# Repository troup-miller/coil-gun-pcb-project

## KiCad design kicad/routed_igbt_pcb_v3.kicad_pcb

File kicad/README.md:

# IGBT PCB — KiCad Project Hand-off

This folder contains a KiCad 7+ project generated from the validated schematic
(`../igbt_schematic.svg` and `../igbt_schematic_notes.md`).

The goal: give you a clean starting point that you open in KiCad, refine,
and route into fab-ready Gerbers, rather than wrestling with the hand-rolled
Gerbers in `../gerber/` which had three known shorts.

## Files

| File | Purpose |
|------|---------|
| `igbt_pcb.kicad_pro` | KiCad project file. Open this in KiCad first. |
| `igbt_pcb.kicad_pcb` | PCB layout with all 26 components placed at their intended positions, ratsnest visible, **no traces yet**. Open in pcbnew. |
| `igbt_pcb.net` | KiCad EESchema-format netlist. 11 nets, 46 pin connections. Defines what connects to what. |
| `igbt_pcb_bom.csv` | Bill of materials with refdes, value, footprint, description. |

## How to use

### Path A: Open the PCB and route directly (fastest)

1. Open KiCad → File → Open Project → select `igbt_pcb.kicad_pro`
2. Open the PCB editor (pcbnew): click `igbt_pcb.kicad_pcb`
3. Components are pre-placed at the coordinates from the schematic intent.
4. **Update footprints from library:** Tools → Update Footprints from Library.
   The footprint *names* in this file are real KiCad library names; pcbnew
   will pull in proper pad geometry, courtyards, silk, etc. on this step.
5. Look at the ratsnest (thin blue lines between pads). Route them as traces
   using your preferred method:
   - Manual: select start pad, "X" to draw track, follow ratsnest
   - Autorouter: Tools → External Plugin → FreeRouting (if installed)
   - Or export to FreeRouting (.dsn export), route, re-import the .ses session
6. Layout intent priorities (from `../igbt_schematic_notes.md` §6):
   - Bottom layer (B.Cu): fill with a continuous **POWER_GROUND** zone (Add Filled Zone → Net = POWER_GROUND → layer = B.Cu)
   - Snubber loop (C1↔R4↔Q1.P3/P4) area < 2 cm²
   - Kelvin lane (Q1.P2 → R3.P2 → D2.P2 → C2.P2 → C3.P2 → U1.P5 → J3) thin and dedicated
   - Twisted pair GATE/KELVIN running from U1 down to Q1
   - Decap caps C2 and C3 within 5 mm of U1.P8/P5
7. Run DRC (design rule check): Inspect → Design Rules Checker.
   Project rules are pre-set: min clearance 0.5 mm, min annular ring 0.25 mm.
8. Generate Gerbers: File → Plot → Layers: F.Cu, B.Cu, F.SilkS, F.Mask, B.Mask, Edge.Cuts → Plot. Then File → Plot → Generate Drill Files.
9. Zip the Gerber + drill files and upload to PCBWay.

### Path B: Import netlist into a fresh KiCad project (cleanest)

If you'd rather start with a clean slate:

1. Open KiCad → New Project → `igbt_pcb_v2.kicad_pro`
2. Open the schematic editor (eeschema). Don't bother drawing — File → Import → Non-KiCad Netlist → select `igbt_pcb.net`. KiCad will create components based on the netlist.
3. Open pcbnew → File → Update PCB from Schematic. Components appear; place them following layout intent.
4. Continue as in Path A from step 5.

## Footprints used (all from KiCad's default libraries)

| Refdes | Component | Footprint |
|--------|-----------|-----------|
| Q1 | MM75GAU65BKX IGBT | `Package_TO_SOT_THT:TO-247-4_Vertical` |
| U1 | HCPL-3120 driver | `Package_DIP:DIP-8_W7.62mm` |
| D1 | C3D30065D FW diode | `Package_TO_SOT_THT:TO-220-3_Vertical` |
| D2 | SMBJ18CA TVS | `Diode_SMD:D_SMB` |
| C1 | 0.47µF snubber pulse cap | `Capacitor_THT:C_Rect_L18.0mm_W5.0mm_P15.00mm` |
| C2 | 0.1µF decap | `Capacitor_THT:C_Disc_D5.0mm_W2.5mm_P5.00mm` |
| C3 | 10µF decap | `Capacitor_THT:CP_Radial_D6.3mm_P2.50mm` |
| R1–R3 | Axial resistors | `Resistor_THT:R_Axial_DIN0207_*` |
| R4 | MP930 snubber damper | `Resistor_THT:R_Axial_DIN0411_*` |
| R5 | Braking resistor | `Resistor_THT:R_Axial_DIN0414_*` |
| J1 | RPi 2-pos terminal | `Connector_PinHeader_5.08mm:PinHeader_1x02_P5.08mm_Vertical` |
| J2, J3 | 1-pos terminals | `TerminalBlock:TerminalBlock_bornier-1_P5.08mm` |
| J4, J5 | 16 AWG wire holes | `TestPoint:TestPoint_THTPad_D4.0mm_Drill3.2mm` |
| TP1–TP9 | Voltmeter probe points | `TestPoint:TestPoint_Pad_D1.5mm` |

If any footprint isn't found in your KiCad install, substitute with the
nearest equivalent — pad pitches are documented in the BOM CSV.

## Net summary

11 nets. The critical isolation requirement:
**KELVIN_RETURN** and **POWER_GROUND** share no copper. They meet only inside Q1's die.

| Net | Members (refdes.pin) |
|-----|----------------------|
| INPUT_VPLUS | J1.1, R1.1 |
| INPUT_GND | J1.2, U1.3 |
| LED_ANODE | R1.2, U1.2 |
| VCC | U1.8, J2.1, C2.1, C3.1, TP1.1 |
| KELVIN_RETURN | U1.5, J3.1, C2.2, C3.2, R3.2, D2.2, Q1.2, TP2.1, TP4.1 |
| GATE_DRIVE_HOT | U1.6, U1.7, R2.1 |
| GATE | R2.2, R3.1, D2.1, Q1.1, TP3.1 |
| POWER_GROUND | J4.1, Q1.3, C1.1, D1.1, D1.3, TP7.1, TP8.1, TP9.1 |
| COLLECTOR | Q1.4, R4.1, R5.1, TP5.1 |
| SNUB_INTERMEDIATE | R4.2, C1.2 |
| FLYBACK_HIGH | R5.2, D1.2, J5.1, TP6.1 |

## Pre-set design rules

The project file ships with these constraints baked in:

- Min copper-to-copper clearance: **0.5 mm**
- Min track width: 0.3 mm
- Min through-hole diameter: 0.3 mm
- Min hole-to-hole spacing: 0.25 mm
- Min annular ring: **0.25 mm**

These match the spec you gave me earlier.

## Verification before fab

After routing, before exporting Gerbers, run all three:
1. **DRC (Design Rule Check)** — must report 0 unresolved violations
2. **ERC (Electrical Rules Check)** — verify nothing was disconnected during placement
3. **3D viewer** — visually confirm component placement makes physical sense

Then plot Gerbers with the following layers selected:
- F.Cu, B.Cu, F.SilkS, F.Mask, B.Mask, Edge.Cuts
- Drill: File → Generate Drill Files → Excellon, Metric units

## Known unknowns

The same five open questions from `../igbt_schematic_notes.md` §8 apply:
switching frequency, coil inductance, brake-resistor value, TVS necessity,
isolated 15 V supply spec.

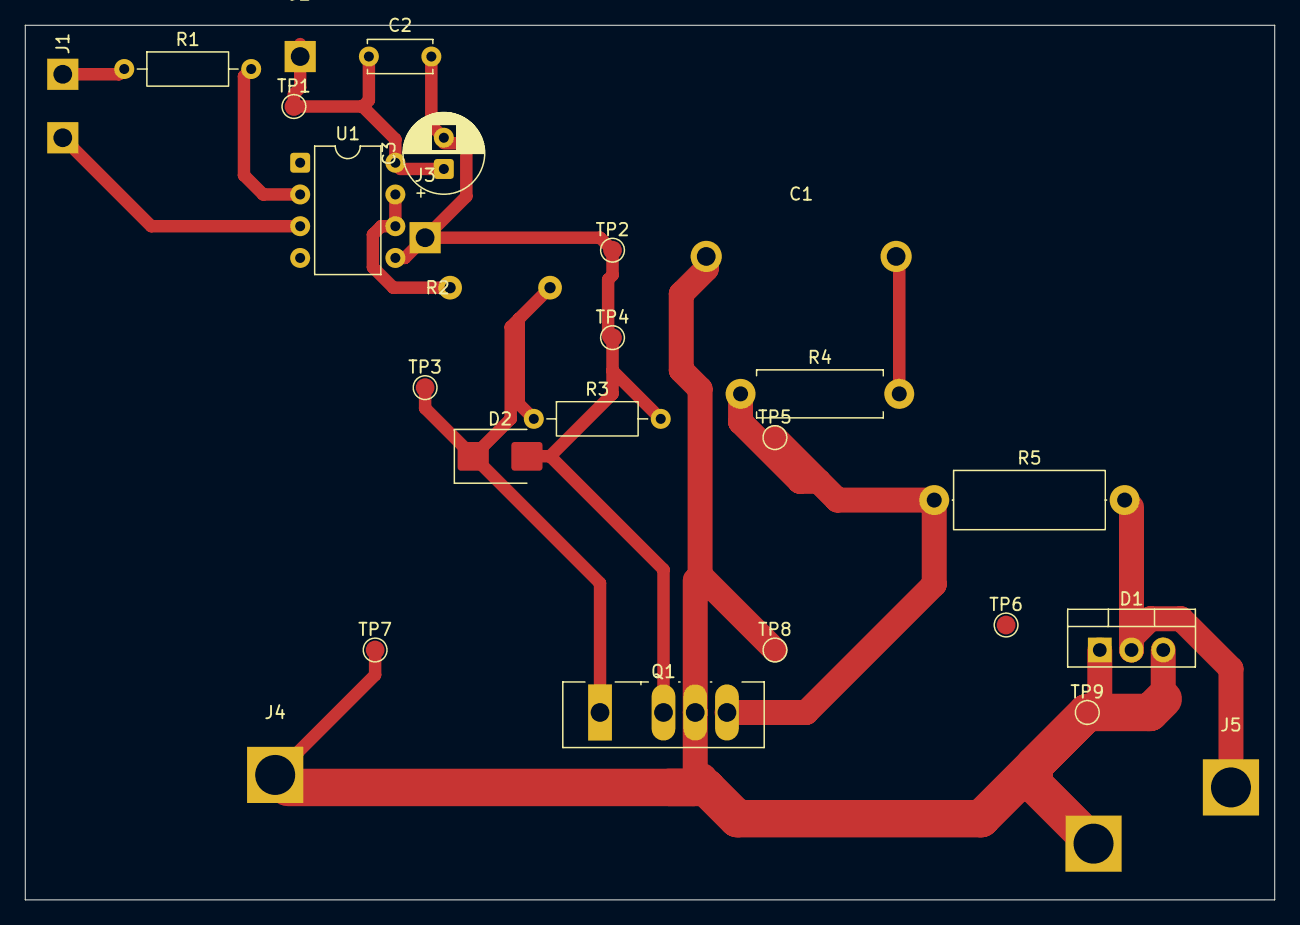
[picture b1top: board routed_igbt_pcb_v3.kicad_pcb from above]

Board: 2 copper layers, 100.0 x 70.0 mm, 26 parts (0 on the bottom side), 11 nets.

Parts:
C1: 0.47uF/600V; C_Rect_L18.0mm_W5.0mm_P15.00mm
C2: 0.1uF; C_Disc_D5.0mm_W2.5mm_P5.00mm
C3: 10uF; CP_Radial_D6.3mm_P2.50mm
D1: C3D30065D; TO-220-3_Vertical
D2: SMBJ18CA; D_SMB
J1: RPi_Input; PinHeader_1x02_P5.08mm_Vertical
J2: +15V; TerminalBlock_bornier-1_P5.08mm
J3: Vee; TerminalBlock_bornier-1_P5.08mm
J4: PSU-_16AWG; TestPoint_THTPad_D4.0mm_Drill3.2mm
J5: Load-_16AWG; TestPoint_THTPad_D4.0mm_Drill3.2mm
Q1: MM75GAU65BKX; TO-247-4_Vertical
R1: 180R/0.25W; R_Axial_DIN0207_L6.3mm_D2.5mm_P10.16mm_Horizontal
R2: 10R/2W; R_Axial_DIN0207_L6.3mm_D2.5mm_P10.16mm_Vertical_L7.0mm
R3: 1.5k/1W; R_Axial_DIN0207_L6.3mm_D2.5mm_P10.16mm_Horizontal
R4: 20R/30W_pulse; R_Axial_DIN0411_L9.9mm_D3.6mm_P12.70mm_Horizontal
R5: Brake_R; R_Axial_DIN0414_L11.9mm_D4.5mm_P15.24mm_Horizontal
TP1: TP_VCC; TestPoint_Pad_D1.5mm
TP2: TP_VEE; TestPoint_Pad_D1.5mm
TP3: TP_GATE; TestPoint_Pad_D1.5mm
TP4: TP_KE; TestPoint_Pad_D1.5mm
TP5: TP_COL; TestPoint_Pad_D1.5mm
TP6: TP_FBK; TestPoint_Pad_D1.5mm
TP7: TP_PGND_A; TestPoint_Pad_D1.5mm
TP8: TP_PGND_B; TestPoint_Pad_D1.5mm
TP9: TP_PGND_C; TestPoint_Pad_D1.5mm
U1: HCPL-3120; DIP-8_W7.62mm

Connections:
COLLECTOR: Q1.4, R4.1, R5.1, TP5.1
FLYBACK_HIGH: D1.2, J5.1, R5.2, TP6.1
GATE: D2.1, Q1.1, R2.2, R3.1, TP3.1
GATE_DRIVE_HOT: R2.1, U1.6, U1.7
INPUT_GND: J1.2, U1.3
INPUT_VPLUS: J1.1, R1.1
KELVIN_RETURN: C2.2, C3.2, D2.2, J3.1, Q1.2, R3.2, TP2.1, TP4.1, U1.5
LED_ANODE: R1.2, U1.2
POWER_GROUND: C1.1, D1.1, D1.3, J4.1, Q1.3, TP7.1, TP8.1, TP9.1
SNUB_INTERMEDIATE: C1.2, R4.2
VCC: C2.1, C3.1, J2.1, TP1.1, U1.8

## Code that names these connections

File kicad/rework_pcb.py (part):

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1. Brake resistor R5 moved out of ballast position; D1+R5 in series across Q1
   collector-emitter (anode at Collector, cathode -> R5 -> Power-Emitter/PGND).
2. TVS D2 replaced with axial through-hole P6KE18CA (DO-15).
3. Snubber R4+C1 placed directly above Q1 PE/Collector pins.
4. HCPL-3120 decoupling caps C2/C3 hugging U1 pins 5 and 8.
5. R3 (gate-emitter pulldown) tight to Q1 Gate/Kelvin-E.
6. R2 (gate series) between U1 Vo and Q1 Gate.
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# -----------------------------------------------------------------------------
PLACEMENTS = {
    # COLD / control side (left, x < 33). Isolation gap at x ~= 33..38.
    'J1':  (3.0,    6.46, 0),    # RPi GPIO header (pin1=INPUT_VPLUS at y=3.92, pin2=INPUT_GND at y=9.0)
    'R1':  (8.0,    4.0,  0),    # 180R input current limiter — horizontal (pads at 8 and 18.16)
    'U1':  (22.0,   6.0,  0),    # HCPL-3120 DIP-8 (pin1=(22,6), pin8=(29.62,6), pin5=(29.62,13.62))
    'C2':  (33.0,   9.81, 90),   # 0.1uF ceramic, vertical, across U1 pins 5 and 8
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# which physical end of the part ends up on which net, without changing the
# circuit. Used here to put the "right" pad nearest the right neighbour.
PAD_NET_UPDATES = [
    # D1: anodes (pins 1, 3) now at COLLECTOR; cathode (pin 2) at brake intermediate
    ('D1',  '1', 'COLLECTOR'),
    ('D1',  '2', 'FLYBACK_HIGH'),
    ('D1',  '3', 'COLLECTOR'),
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            sys.exit("ERROR: could not load Diode_THT:D_DO-15_P10.16mm_Horizontal")
        d2_new.SetReference('D2')
        d2_new.SetValue('P6KE18CA')
        # D2 is a bidirectional TVS; nets carry over: pin1=GATE, pin2=KELVIN_RETURN
        for pad in d2_new.Pads():
            if pad.GetNumber() == '1':
                pad.SetNet(nets['GATE'])
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
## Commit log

2026-05-18 initial commit tidy up
